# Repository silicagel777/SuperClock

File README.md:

# LED Matrix Super Clock

A DIY desk clock with retro-style dot matrix display

## Features

- A retro-style dot matrix display:
    - 17x6 5mm LED matrix
    - Different LED colors for main area, status bar and number separator
    - No flickering, ghosting or uneven brightness
    - High refresh rate of 460Hz
    - 8-bit global brightness and 3-bit per-pixel brightness
    - Global brightness is automatically (and smoothly) adjusted by ambient conditions, just like on your phone!
- Accurate timekeeping:
    - Temperature-compensated crystal clock (DS3231SN chip)
    - Backup power to keep the clock ticking (CR2032 battery)
    - Displays minute, hour, day, weekday, month, year and even ambient temperature
    - Green status bar tracks seconds (incremented every 4s)
    - Five alarms with melody
- Intuitive (kinda) user interface with three buttons
- Cool acrylic glass frame
- Powered by any USB brick through a Type-B cable
    - Finally, a reason to pick up that old printer cable from your drawer!
- Built around ATmega32 microcontroller, with firmware written in C++
    - Uses **every** I/O pin on ATmega32, no wasted potential!
- No AI and no internet connection! (yup, that's a feature nowadays...)
- Totally open-source!

## Documentation

- [Hardware docs](docs/hardware.md)
    - Includes schematics, design files, parts list and even assembly tips
- [Frame docs](docs/frame.md)
    - Describes the acrylic glass frame
- [Software docs](docs/firmware.md)
    - How to flash firmware or set up development tools if you want to modify it
- [LED matrix notes](docs/matrix.md)
    - Notes on how the LED matrix works
- [User manual](docs/manual.md)
    - What do these buttons do?!

## TODO list

- [x] Write this readme
- [x] Make first public release
- [ ] Animated minute/hour transitions
- [ ] Reorganize font system
- [ ] More levels for highest and lowest brightness?
- [ ] Use C++ namespaces?
- [ ] Abstractions for pins and timers?
- [ ] Snake mode? :D

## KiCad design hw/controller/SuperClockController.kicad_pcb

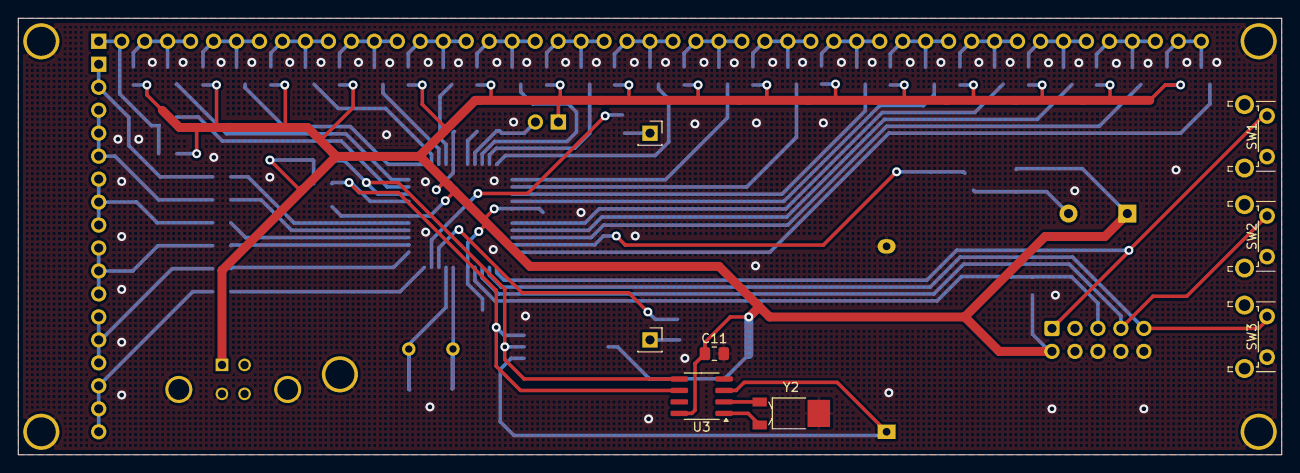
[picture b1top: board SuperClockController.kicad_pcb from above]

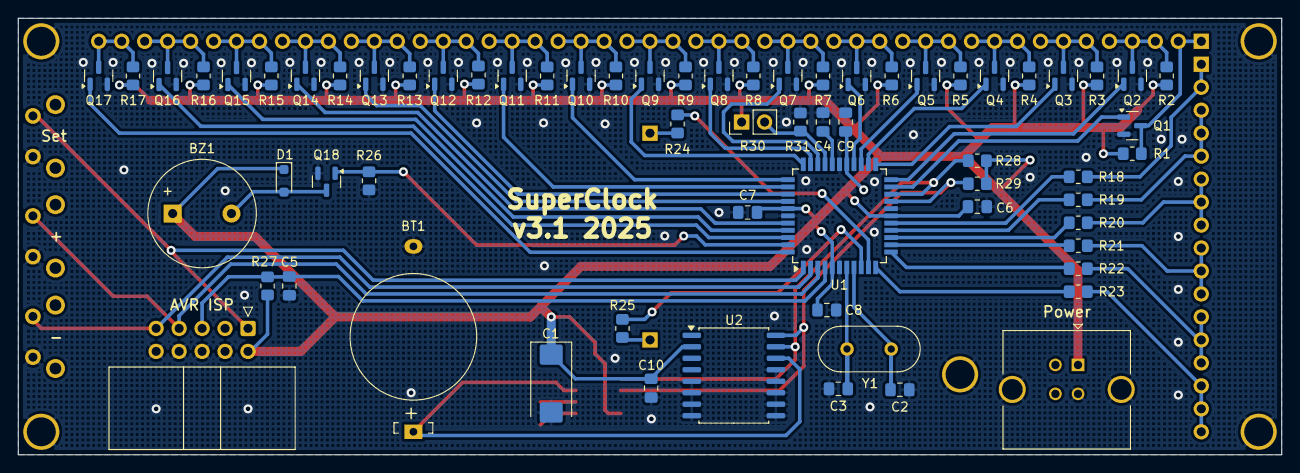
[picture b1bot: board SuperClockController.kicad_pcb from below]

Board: 2 copper layers, 139.7 x 48.3 mm, 82 parts (67 on the bottom side), 67 nets.

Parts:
BT1: CR2032; Battery_CR2032
BZ1: Passive Buzzer 42R; Buzzer_12x8.5
C1: 100uF; CP_EIA-7343-31_Kemet-D_Pad2.25x2.55mm_HandSolder
C2, C3: 12pF; C_0805_2012Metric_Pad1.18x1.45mm_HandSolder
C4, C5, C6, C7, C8, C9, C10, C11: 0.1uF; C_0805_2012Metric_Pad1.18x1.45mm_HandSolder
D1: 1N5819WS; D_SOD-323_HandSoldering
H1, H2, H3, H4, H5: MountingHole_Pad; MountingHole_3.2mm_M3_SmallPad
J1: Led Cathodes; PinSocket_1x49_P2.54mm_Vertical
J2: Led Anodes; PinSocket_1x17_P2.54mm_Vertical
J3: Yellow LED 0; PinSocket_1x01_P2.54mm_Vertical
J4: Yellow LED 1; PinSocket_1x01_P2.54mm_Vertical
J5: USB_A; USB_B_TE_5787834_Vertical
J6: ATmega ISP; IDC-Header_2x05_P2.54mm_Horizontal
Q1, Q2, Q3, Q4, Q5, Q6, Q7, Q8, Q9, Q10, Q11, Q12, Q13, Q14, Q15, Q16, Q17, Q18: 2N7002K; SOT-23
R1, R2, R3, R4, R5, R6, R7, R8, R9, R10, R11, R12, R13, R14, R15, R16, R17: R_0805_2012Metric_Pad1.20x1.40mm_HandSolder
R18, R19, R20, R21, R22, R24, R25: 220; R_0805_2012Metric_Pad1.20x1.40mm_HandSolder
R23: 3.3K; R_0805_2012Metric_Pad1.20x1.40mm_HandSolder
R26, R31: 10K; R_0805_2012Metric_Pad1.20x1.40mm_HandSolder
R27, R28, R29: 4.7K; R_0805_2012Metric_Pad1.20x1.40mm_HandSolder
R30: GL5516; PinHeader_1x02_P2.54mm_Vertical
SW1, SW2, SW3: SW_Push; SW_Tactile_SPST_Angled_PTS645Vx39-2LFS
U1: ATmega32A-A; TQFP-44_10x10mm_P0.8mm
U2: DS3231SN; SOIC-16W_7.5x10.3mm_P1.27mm
U3: DS1307ZN; SOIC-8_3.9x4.9mm_P1.27mm
Y1: 16MHz; Crystal_HC49-U_Vertical
Y2: 32.768kHz; Crystal_SMD_MicroCrystal_MS1V-T1K

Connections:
+5V: BZ1.1 (+), C1.1, C6.1, C7.1, C8.1, C9.1, C10.1, C11.1, D1.1 (K), J5.1 (VBUS), J6.2, R1.2, R2.2, R3.2, R4.2, R5.2, R6.2, R7.2, R8.2, R9.2, R10.2, R11.2, R12.2, R13.2, R14.2, R15.2, R16.2, R17.2, R27.1, R28.1, R29.1, R30.1, U1.5 (VCC), U1.17 (VCC), U1.27 (AVCC), U1.38 (VCC), U2.2 (VCC), U3.8 (VCC)
/BUTTON_0: J6.1, SW1.1, U1.1 (PB5)
/BUTTON_1: J6.7, SW2.1, U1.3 (PB7)
/BUTTON_2: J6.9, SW3.1, U1.2 (PB6)
/BUZZER: Q18.1 (G), R26.1, U1.43 (PB3)
/ISP_RESET: C5.1, J6.5, R27.2, U1.4 (~RESET)
/LED_A0_RED: J2.1, J2.2, R18.2
/LED_A1_RED: J2.3, J2.4, J2.5, R19.2
/LED_A2_RED: J2.6, J2.7, J2.8, R20.2
/LED_A3_RED: J2.9, J2.10, J2.11, R21.2
/LED_A4_RED: J2.12, J2.13, J2.14, R22.2
/LED_A5_GREEN: J2.15, J2.16, J2.17, R23.2
/LED_A6_YELLOW: J3.1, R24.2
/LED_A7_YELLOW: J4.1, R25.2
/LED_C0: J1.1, J1.2, Q1.3 (D), R1.1
/LED_C1: J1.3, J1.4, J1.5, Q2.3 (D), R2.1
/LED_C2: J1.6, J1.7, J1.8, Q3.3 (D), R3.1
/LED_C3: J1.9, J1.10, J1.11, Q4.3 (D), R4.1
/LED_C4: J1.12, J1.13, J1.14, Q5.3 (D), R5.1
/LED_C5: J1.15, J1.16, J1.17, Q6.3 (D), R6.1
/LED_C6: J1.18, J1.19, J1.20, Q7.3 (D), R7.1
/LED_C7: J1.21, J1.22, J1.23, Q8.3 (D), R8.1
/LED_C8: J1.24, J1.25, J1.26, Q9.3 (D), R9.1
/LED_C9: J1.27, J1.28, J1.29, Q10.3 (D), R10.1
/LED_C10: J1.30, J1.31, J1.32, Q11.3 (D), R11.1
/LED_C11: J1.33, J1.34, J1.35, Q12.3 (D), R12.1
/LED_C12: J1.36, J1.37, J1.38, Q13.3 (D), R13.1
/LED_C13: J1.39, J1.40, J1.41, Q14.3 (D), R14.1
/LED_C14: J1.42, J1.43, J1.44, Q15.3 (D), R15.1
/LED_C15: J1.45, J1.46, J1.47, Q16.3 (D), R16.1
/LED_C16: J1.48, J1.49, Q17.3 (D), R17.1
/LIGHT_SENSE: R30.2, R31.1, U1.30 (PA7)
/MCU_A0: R18.1, U1.16 (PD7)
/MCU_A1: R19.1, U1.15 (PD6)
/MCU_A2: R20.1, U1.14 (PD5)
/MCU_A3: R21.1, U1.13 (PD4)
/MCU_A4: R22.1, U1.12 (PD3)
/MCU_A5: R23.1, U1.11 (PD2)
/MCU_C0: Q1.1 (G), U1.21 (PC2)
/MCU_C1: Q2.1 (G), U1.22 (PC3)
/MCU_C2: Q3.1 (G), U1.23 (PC4)
/MCU_C3: Q4.1 (G), U1.24 (PC5)
/MCU_C4: Q5.1 (G), U1.25 (PC6)
/MCU_C5: Q6.1 (G), U1.26 (PC7)
/MCU_C6: Q7.1 (G), U1.31 (PA6)
/MCU_C7: Q8.1 (G), U1.32 (PA5)
/MCU_C8: Q9.1 (G), U1.33 (PA4)
/MCU_C9: Q10.1 (G), U1.34 (PA3)
/MCU_C10: Q11.1 (G), U1.35 (PA2)
/MCU_C11: Q12.1 (G), U1.36 (PA1)
/MCU_C12: Q13.1 (G), U1.37 (PA0)
/MCU_C13: Q14.1 (G), U1.40 (PB0)
/MCU_C14: Q15.1 (G), U1.41 (PB1)
/MCU_C15: Q16.1 (G), U1.42 (PB2)
/MCU_C16: Q17.1 (G), U1.44 (PB4)
/MCU_DOT0: R24.1, U1.10 (PD1)
/MCU_DOT1: R25.1, U1.9 (PD0)
/RTC_BATTERY: BT1.1 (+), U2.14 (VBAT), U3.3 (VBAT)
/RTC_SCL: R29.2, U1.19 (PC0), U2.16 (SCL), U3.6 (SCL)
/RTC_SDA: R28.2, U1.20 (PC1), U2.15 (SDA), U3.5 (SDA)
GND: BT1.2 (-), C1.2, C2.2, C3.2, C4.2, C5.2, C6.2, C7.2, C8.2, C9.2, C10.2, C11.2, H1.1, H2.1, H3.1, H4.1, H5.1, J5.4 (GND), J5.5 (Shield), J6.4, J6.6, J6.8, J6.10, Q1.2 (S), Q2.2 (S), Q3.2 (S), Q4.2 (S), Q5.2 (S), Q6.2 (S), Q7.2 (S), Q8.2 (S), Q9.2 (S), Q10.2 (S), Q11.2 (S), Q12.2 (S), Q13.2 (S), Q14.2 (S), Q15.2 (S), Q16.2 (S), Q17.2 (S), Q18.2 (S), R26.2, R31.2, SW1.2, SW2.2, SW3.2, U1.6 (GND), U1.18 (GND), U1.28 (GND), U1.39 (GND), U2.5 (GND), U2.6 (GND), U2.7 (GND), U2.8 (GND), U2.9 (GND), U2.10 (GND), U2.11 (GND), U2.12 (GND), U2.13 (GND), U3.4 (GND), Y2.3
unnamed: BZ1.2 (-), D1.2 (A), Q18.3 (D)
unnamed: C4.1, U1.29 (AREF)
unnamed: C2.1, U1.8 (XTAL1), Y1.1
unnamed: C3.1, U1.7 (XTAL2), Y1.2
unnamed: U3.1 (X1), Y2.1
unnamed: U3.2 (X2), Y2.2

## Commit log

2025-01-07 Reorganize drivers
2025-01-07 Use timer interrupts in display driver
2025-01-07 Fix scheduler
2025-01-07 Add buzzer driver
2025-01-07 Pixel brigtness test
2025-01-07 Global brightness test
2025-01-08 Display driver improvemets
    - Increase refresh rate
    - Special workarounds for lowest and highest brigtness
    - Support per-pixel brightness (with low refresh rate)
    - Bitmap write API
    - Transpose display buffer layout to make bitmaps more readable in code
2025-01-08 Support writing numbers
2025-01-08 Support display clear
2025-01-08 Implement I2C driver, actual ticking clock demo
2025-01-09 RTC driver test
2025-01-09 Auto-brigtness test
2025-01-09 Fix per-pixel brigtness blinking
2025-01-09 Workaround for ghosting on low brigtness
2025-01-12 Button read test
2025-01-12 Clock page test
    Also, various type and bug fixes
2025-01-12 Temperature read test
2025-01-12 Time setup test
2025-01-12 Fix non-uniform column intensity for lowest brightness
2025-01-14 Update usbasp speed settings
2025-01-14 Reduce minimal brightness at the expense of some RAM
2025-01-14 Display double buffering
2025-01-14 Font system test
2025-01-14 String support in display driver
2025-01-14 Remove snprintf usage to save some flash memory
2025-01-14 Dynamic page switching test
2025-01-14 Move page environment to a seperate struct
2025-01-15 More options for task removal
2025-01-15 Replace callback wrappers with templates
2025-01-15 Use constructors and destructors instead of show and hide in pages
2025-01-15 Remove empty default page and extract some nested stuff
2025-01-15 Move pages to separate directories
2025-01-15 Move new to util
2025-01-15 Fix typo
2025-01-15 Increase tasks buffer
2025-01-15 Use template-style addTask in all places
2025-01-15 Change pages through scheduer
    Now, page code that does something after calling `changePage` is safe
2025-01-15 Update TODO and comments
2025-01-16 Buffered RTC driver
2025-01-16 Update TODO
2025-01-16 Use 16-bit delays
    There is no need for them to be longer
2025-01-16 Add removeTasks for member callbacks
2025-01-16 Clock setup page
2025-01-16 Tasks with auto-reload
2025-01-16 Optimize for size
2025-01-16 Update demo mode
2025-01-16 Use more letters and less number in clock mode
2025-01-16 Alarm module
2025-01-16 Alarm view page
2025-01-16 Use references for rtcTime
2025-01-16 Rename DemoPage to TestPage
2025-01-16 Support passing a pointer-sized argument to page
2025-01-16 Alarm setup page
2025-01-16 Alarm alert page (without sound yet)
2025-01-16 Support negative temperatures
2025-01-17 Alarm melody
2025-01-17 Nicer animation for alarm alert page
2025-01-17 A slightly better progmem abstraction
2025-01-17 Implement missing destructors
    Also enable interrupts through a separate module
2025-01-17 Eeprom abstraction + move alarm module out of drivers
2025-01-17 Button driver cleanup
2025-01-18 Make button driver more noise-tolerant by ignoring short pulses
2025-01-18 Add harware design files to repo
2025-01-18 Make LED holes smaller
    The 0.9 hole size turned out to be too wiggly, 0.8 should work better
2025-01-19 Mention buzzer resistance on schematic
2025-01-20 Controller PCB revision 3.1
    - Add cathode pull-ups. It seems to be the only proper way to deal with ghosting and flickering on lowest brightness
    - Connect all anodes to one MCU port, should provide more opportunities to software.
    - Use smaller silk-screen outline for CR2032 holder (the previous one was visibly offset for my battery holder).
    - Update component numbering with a more sensible scheme: cathode FETs and resistors are now numbers 1-17.
    - Use bigger footprint and bigger value for power input capacitor.
    - Add missing capacitor to one of MCU power pins.
2025-01-21 Link libmath
    Not used yet, but might be helpful later
2025-01-21 Make output of avr-size more helpful
    It now shows memory use percentages
2025-01-22 Add schematics in PDF
2025-03-10 Reorder stuff on schematic for better readability + update to KiCAD 9.0
2025-03-10 Replace IRLML2505 to AO3416A
    This one claims to have ESD-protected gates, should be easier to handle
2025-03-15 Fix month/day ordering
2025-03-15 Update display driver to match controller rev. 3.1 pinout
2025-03-15 Preserve EEPROM on chip erase
    Let's not reset alarms on firmware update
2025-03-15 Use exponential filter for brightness regulation
2025-03-15 Define alpha through frequency and delta in exponential filter
    To my delight, GCC optimizes out these calculations, so binary size does not change, but the meaning of alpha coefficient becomes much more clear.
2025-04-15 Add README
2025-04-15 Add Github action to build stuff
2025-04-15 Minor documentation fixes
2025-08-13 Add stopwatch mode
2026-02-21 Add panic driver and use it in scheduler
    A failed `addTask` is something that generally can't be recovered from, so let's halt with an error code instead of returning a value that is never checked.
2026-02-21 DS3231 calibration support
    It is now possible to set the DS3231 "aging" register value during clock setup
2026-02-21 Add NOP to infinite loop in panic handler
    Just to be sure future compiler versions won't optimize the loop out
2026-04-23 Fix alarm saving bug and a few other minor issues
2026-05-20 More consistent beeper response for stopwatch actions
2026-05-20 Mark R1-R17 as DNP, replace AO3416 with 2N7002K and update docs.
    It turned out that green LEDs do not like the reverse voltage at all, and they started slowly failing in a few months. So let's combat LED ghosting by using MOSFETs with lower parasitic capacitance i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
2026-05-20 Fix a few minor mistakes and typos in docs
